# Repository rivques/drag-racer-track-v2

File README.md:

# drag-racer-track-v2
A new and improved version of [mini-drag-racetrack](https://github.com/rivques/mini-drag-racetrack).

## Contact Me
While this racetrack was designed to be maintainable by people other than me, please don't hesitate to contact me if you run into an issue that these docs don't cover.
You can open an issue on this repository, email me at `web (at) rivques (dot) dev`, or check [my website](https://rivques.dev) for my latest contact information.

## Troubleshooting
See [troubleshooting.md](docs/troubleshooting.md)

## How to Use
See [how_to_use.md](docs/how_to_use.md)

## Bill Of Materials
See [bill_of_materials.md](docs/bill_of_materials.md)

## Assembly From Storage
See [assembly_from_storage.md](docs/assembly_from_storage.md)

## Assembly From Scratch
See [assembly_from_scratch.md](docs/assembly_from_scratch.md)

## CAD
See [the CAD folder](https://github.com/rivques/drag-racer-track-v2/tree/main/cad) or [this Onshape document](https://cvilleschools.onshape.com/documents/214ca204c2fbd1332e8a9828/w/7c57c6410ddb9c7d8c5eff08/e/c34b4d3245393d7aa3c3b2bb).

## Project Proposal
Available at [this Google doc](https://docs.google.com/document/d/1fPM3jAb2btpLcQTNEUYPZXAGJ7guPSih1aArkj4l1_s/edit?usp=sharing), viewable from a CCS account.

## Photos
Various photos of the assembly are available in the [doc-pics](https://github.com/rivques/drag-racer-track-v2/tree/main/doc-pics) directory.

## Circuit Diagrams
Schematics and board layouts are available in the [circuit/outputs](https://github.com/rivques/drag-racer-track-v2/tree/main/circuit/outputs) directory.

### Commmunication
The three modules communicate over straight-through CAT-5 (aka Ethernet) cable. This pinout is constructed to allow near-unambiguous determination by the main processor of 1. if a cable is connected and 2. if the cable is connected to the motors or the screen.

The pinout is as follows (assuming T568A terminations):

#### Main-Motor (purpose and direction from Main's perspective):

RJ-45 Pin # | T568A color | Pico pin | Purpose | Direction | Notes
---|---|---|---|---|---
1|Wh/Gr|GND|GND|Bidirectional|Shared ground reference
2|Gr|GP0|TX|OUTPUT|UART 8N1@9600 baud
3|Wh/Or|GP2|Discrim|INPUT|Tied to GND at Motor
4|Bl|NC|NC||
5|Wh/Bl|3V3OUT|3V3|OUTPUT|
6|Or|GP1|RX|INPUT|UART 8N1@9600 baud
7|Wh/Br|GP3|Presence|INPUT|Tied to GND at Motor
8|Br|NC|NC||

#### Main-Button Controller (purpose and direction from Main's perspective):

RJ-45 Pin # | T568A color | Pico pin | Purpose | Direction | Notes
---|---|---|---|---|---
1|Wh/Gr|GND|GND|OUTPUT|
2|Gr|GP17|LED_RACE|OUTPUT|
3|Wh/Or|GP8|Discrim|INPUT|Tied to RESET at Controller
4|Bl|GP4|RESET|INPUT|
5|Wh/Bl|GP16|LED_ARM|OUTPUT|
6|Or|GP5|ARM|INPUT|
7|Wh/Br|GP7|Presence|INPUT|Tied to GND at Controller
8|Br|GP6|RACE|INPUT|

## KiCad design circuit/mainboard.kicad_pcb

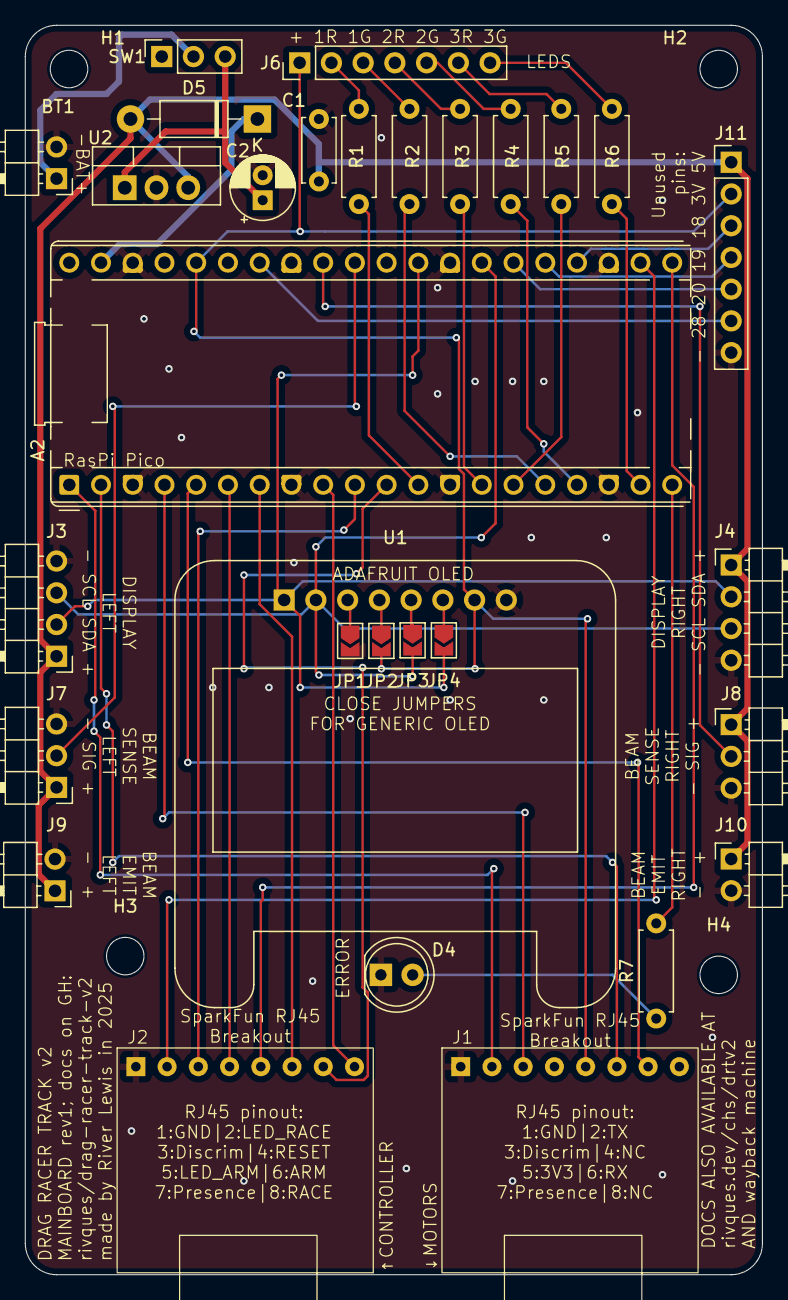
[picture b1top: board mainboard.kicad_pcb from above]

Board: 2 copper layers, 59.0 x 100.0 mm, 34 parts (0 on the bottom side), 43 nets.

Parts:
A2: RaspberryPi_Pico; RaspberryPi_Pico_Common_THT
BT1: 5xAA; PinHeader_1x02_P2.54mm_Horizontal
C1: 0.1; C_Disc_D5.0mm_W2.5mm_P5.00mm
C2: 0.22; CP_Radial_D5.0mm_P2.00mm
D4: ERROR_LED; LED_D5.0mm
D5: 1N4001; D_DO-41_SOD81_P10.16mm_Horizontal
H1, H2, H3, H4: MountingHole; MountingHole_3mm
J1: MOTOR_CONN; RJ45_Breakout_2.54mm
J2: CTRLR_CONN; RJ45_Breakout_2.54mm
J3: DISP_LEFT; PinHeader_1x04_P2.54mm_Horizontal
J4: DISP_RIGHT; PinHeader_1x04_P2.54mm_Horizontal
J6: LED_Conn; PinHeader_1x07_P2.54mm_Vertical
J7: BEAM_SENSE_LEFT; PinHeader_1x03_P2.54mm_Horizontal
J8: BEAM_SENSE_RIGHT; PinHeader_1x03_P2.54mm_Horizontal
J9: BEAM_EMIT_LEFT; PinHeader_1x02_P2.54mm_Horizontal
J10: BEAM_EMIT_RIGHT; PinHeader_1x02_P2.54mm_Horizontal
J11: UNUSED_PINS; PinHeader_1x07_P2.54mm_Vertical
JP1, JP2, JP3, JP4: SolderJumper-2_P1.3mm_Open_TrianglePad1.0x1.5mm
R1, R2, R3, R4, R5, R6, R7: 220; R_Axial_DIN0207_L6.3mm_D2.5mm_P7.62mm_Horizontal
SW1: POWER; PinSocket_1x03_P2.54mm_Vertical
U1: OLED_128x64; Adafruit_SSD1306_No_Mounting_Holes
U2: LM7805_TO220; TO-220-3_Vertical

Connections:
5V: C1.1, D5.2 (A), J3.1, J4.1, J7.1, J8.1, J9.1, J10.1, J11.1, U2.3 (VO)
+3V3: A2.36 (3V3), J1.5, J6.1, J11.2, JP2.2 (B), U1.7 (VIN)
/CTRL_ARM: A2.7 (GPIO5), J2.6
/CTRL_DISCRIM: A2.10 (GPIO7), J2.3
/CTRL_LEDARM: A2.21 (GPIO16), J2.5
/CTRL_LEDRACE: A2.22 (GPIO17), J2.2
/CTRL_PRES: A2.11 (GPIO8), J2.7
/CTRL_RACE: A2.9 (GPIO6), J2.8
/CTRL_RESET: A2.6 (GPIO4), J2.4
/ERROR_LED: A2.20 (GPIO15), R7.2
/GPIO18: A2.24 (GPIO18), J11.3
/GPIO19: A2.25 (GPIO19), J11.4
/GPIO20: A2.26 (GPIO20), J11.5
/GPIO28_ADC2: A2.34 (GPIO28_ADC2), J11.6
/LBEAM_SIG: A2.31 (GPIO26_ADC0), J7.2
/LED1G: A2.16 (GPIO12), R2.1
/LED1R: A2.12 (GPIO9), R1.1
/LED2G: A2.17 (GPIO13), R4.1
/LED2R: A2.14 (GPIO10), R3.1
/LED3G: A2.19 (GPIO14), R6.1
/LED3R: A2.15 (GPIO11), R5.1
/MTR_DISCRIM: A2.4 (GPIO2), J1.3
/MTR_PRES: A2.5 (GPIO3), J1.7
/MTR_RX: A2.2 (GPIO1), J1.6
/MTR_TX: A2.1 (GPIO0), J1.2
/PRESWITCH: BT1.1 (+), SW1.2 (B)
/RBEAM_SIG: A2.32 (GPIO27_ADC1), J8.2
/SCL: A2.27 (GPIO21), J3.3, J4.3, JP3.2 (B), U1.2 (CLK)
/SDA: A2.29 (GPIO22), J3.2, J4.2, JP4.2 (B), U1.1 (DATA)
/VBAT: C2.1, SW1.3 (C), U2.1 (VI)
/VSYS: A2.39 (VSYS), D5.1 (K)
GND: A2.3 (GND), A2.8 (GND), A2.13 (GND), A2.18 (GND), A2.23 (GND), A2.28 (GND), A2.38 (GND), BT1.2 (-), C1.2, C2.2, D4.1 (K), J1.1, J2.1, J3.4, J4.4, J7.3, J8.3, J9.2, J10.2, J11.7, JP1.2 (B), U1.8 (GND), U2.2 (GND)
unnamed: D4.2 (A), R7.1
unnamed: J6.2, R1.2
unnamed: J6.3, R2.2
unnamed: J6.4, R3.2
unnamed: J6.5, R4.2
unnamed: J6.6, R5.2
unnamed: J6.7, R6.2
unnamed: JP1.1 (A), U1.3 (A0)
unnamed: JP2.1 (A), U1.4 (RST)
unnamed: JP3.1 (A), U1.5 (CS)
unnamed: JP4.1 (A), U1.6 (3VO)

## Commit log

2025-01-13 port launch.json to macos
2025-01-14 test beam breaks and start planning wiring
2025-01-14 redo RJ45 wiring
2025-01-14 add pico pin columnn
2025-01-15 get started on schematic
2025-01-15 schematic first pass
2025-01-15 add LEDs to controller
2025-01-15 kicad deleted some files ig lol
2025-01-15 add footprints and organize sheet
2025-01-15 initial pcb layout
2025-01-15 route PCB
2025-01-15 refine PCB
2025-01-16 This is the board that was produced as rev1
2025-01-16 write mainboard firmware (untested)
2025-01-21 add circuit for motor controller
2025-01-22 add motor controller wiring diagram
2025-01-23 adjust left servo wire
2025-01-24 move conn led and power connection
2025-01-24 update schematic to match wiring diagram
2025-01-27 add some pics of the motor controller
2025-01-29 write motorcontroller firmware (half-tested)
2025-02-05 start making the physical board work
2025-02-06 start to debug mainboard code
2025-02-06 fix short on motor controller board - oops
2025-02-11 assorted bugfixes
2025-03-03 flip around motorcon rj45
2025-03-03 use a ground wire for that led
2025-03-14 add switch and power to motor controller
2025-03-17 fix some bugs
2025-03-18 fix right server port
2025-03-19 add circuit for race controller
2025-03-20 fix flipped rj-45 port in controller
2025-04-14 write a bit of docs
2025-04-15 more docs
2025-04-16 small improvements + bugfixes to firmware
2025-04-17 reorganize docs and work on electronics BOM
2025-04-24 docs!
2025-05-02 refine README a bit
2025-05-02 fix link and crop image
2025-05-05 make docs conform to markdown better
2025-05-05 switch some links to point to the github repo
2025-05-05 fix more tables because markdown is picky
